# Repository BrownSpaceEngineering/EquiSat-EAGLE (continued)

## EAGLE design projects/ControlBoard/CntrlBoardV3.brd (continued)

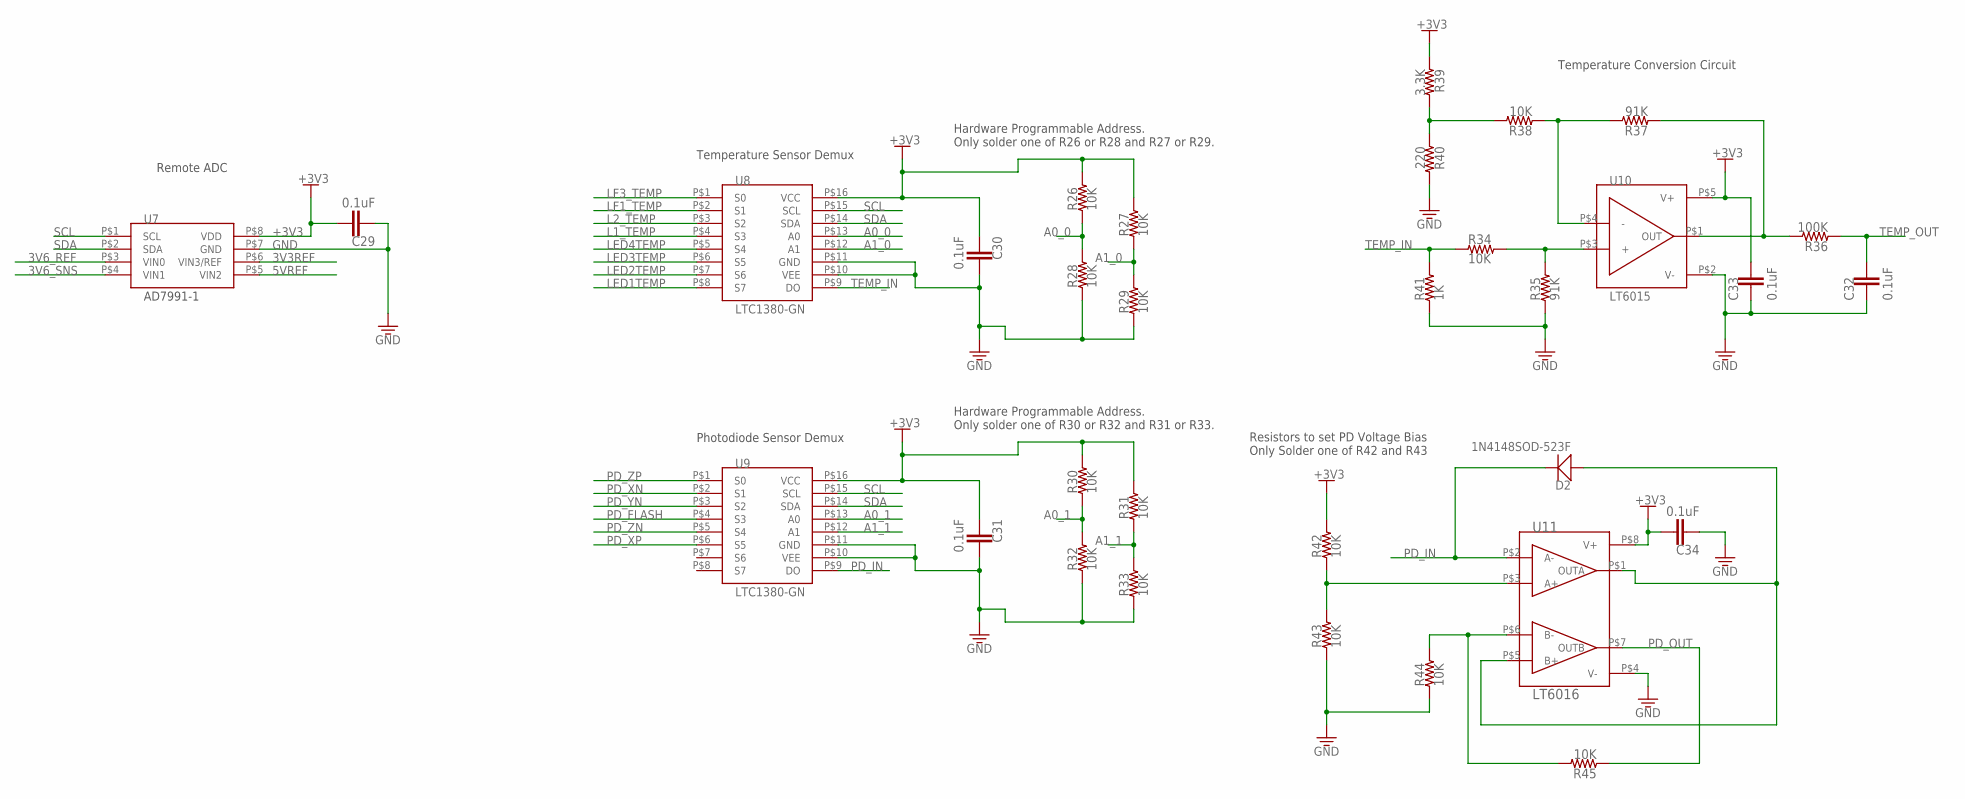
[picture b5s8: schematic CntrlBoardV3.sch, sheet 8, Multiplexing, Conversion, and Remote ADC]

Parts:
C29, C30, C31, C32, C33, C34: 0.1uF; 0805
D2: 1N4148SOD-523F; SOD-523F
R26, R27, R28, R29, R30, R31, R32, R33, R34, R38, R42, R43, R44, R45: 10K; 0805
R35, R37: 91K; 0805
R36: 100K; 0805
R39: 3.3K; 0805
R40: 220; 0805
R41: 1K; 0805
U7: AD7991-1; SOT-23-8
U8, U9: LTC1380-GN; SSOP-16-NARROW
U10: LT6015; TSOT23-5
U11: LT6016; MSOP-8

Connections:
3V3REF: U7.P$6 (VIN3/REF); also elsewhere on the board
3V6_REF: U7.P$3 (VIN0); also elsewhere on the board
3V6_SNS: U7.P$4 (VIN1); also elsewhere on the board
5VREF: U7.P$5 (VIN2); also elsewhere on the board
+3V3: C29.1, C30.2, C31.2, C33.1, C34.1, R26.2, R27.2, R30.2, R31.2, R39.1, R42.2, U7.P$8 (VDD), U8.P$16 (VCC), U9.P$16 (VCC), U10.P$5 (V+), U11.P$8 (V+); also elsewhere on the board
A0_0: R26.1, R28.2, U8.P$13 (A0)
A0_1: R30.1, R32.2, U9.P$13 (A0)
A1_0: R27.1, R29.2, U8.P$12 (A1)
A1_1: R31.1, R33.2, U9.P$12 (A1)
GND: C29.2, C30.1, C31.1, C32.2, C33.2, C34.2, R28.1, R29.1, R32.1, R33.1, R35.1, R40.2, R41.1, R43.1, R44.1, U7.P$7 (GND), U8.P$10 (VEE), U8.P$11 (GND), U9.P$10 (VEE), U9.P$11 (GND), U10.P$2 (V-), U11.P$4 (V-); also elsewhere on the board
L1_TEMP: U8.P$4 (S3); also elsewhere on the board
L2_TEMP: U8.P$3 (S2); also elsewhere on the board
LED1TEMP: U8.P$8 (S7); also elsewhere on the board
LED2TEMP: U8.P$7 (S6); also elsewhere on the board
LED3TEMP: U8.P$6 (S5); also elsewhere on the board
LED4TEMP: U8.P$5 (S4); also elsewhere on the board
LF1_TEMP: U8.P$2 (S1); also elsewhere on the board
LF3_TEMP: U8.P$1 (S0); also elsewhere on the board
unnamed: R34.2, R35.2, U10.P$3 (+)
unnamed: R38.2, R39.2, R40.1
unnamed: R37.2, R38.1, U10.P$4 (-)
unnamed: R36.2, R37.1, U10.P$1 (OUT)
unnamed: D2.A, U11.P$1 (OUTA), U11.P$5 (B+)
unnamed: R42.1, R43.2, U11.P$3 (A+)
unnamed: R44.2, R45.2, U11.P$6 (B-)
PD_FLASH: U9.P$4 (S3); also elsewhere on the board
PD_IN: D2.C, U9.P$9 (DO), U11.P$2 (A-)
PD_OUT: R45.1, U11.P$7 (OUTB); also elsewhere on the board
PD_XN: U9.P$2 (S1); also elsewhere on the board
PD_XP: U9.P$6 (S5); also elsewhere on the board
PD_YN: U9.P$3 (S2); also elsewhere on the board
PD_ZN: U9.P$5 (S4); also elsewhere on the board
PD_ZP: U9.P$1 (S0); also elsewhere on the board
SCL: U7.P$1 (SCL), U8.P$15 (SCL), U9.P$15 (SCL); also elsewhere on the board
SDA: U7.P$2 (SDA), U8.P$14 (SDA), U9.P$14 (SDA); also elsewhere on the board
TEMP_IN: R34.1, R41.2, U8.P$9 (DO)
TEMP_OUT: C32.1, R36.1; also elsewhere on the board

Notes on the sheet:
Hardware Programmable Address. Only solder one of R26 or R28 and R27 or R29.
Temperature Sensor Demux
Hardware Programmable Address. Only solder one of R30 or R32 and R31 or R33.
Photodiode Sensor Demux
Temperature Conversion Circuit
Resistors to set PD Voltage Bias Only Solder one of R42 and R43
Remote ADC

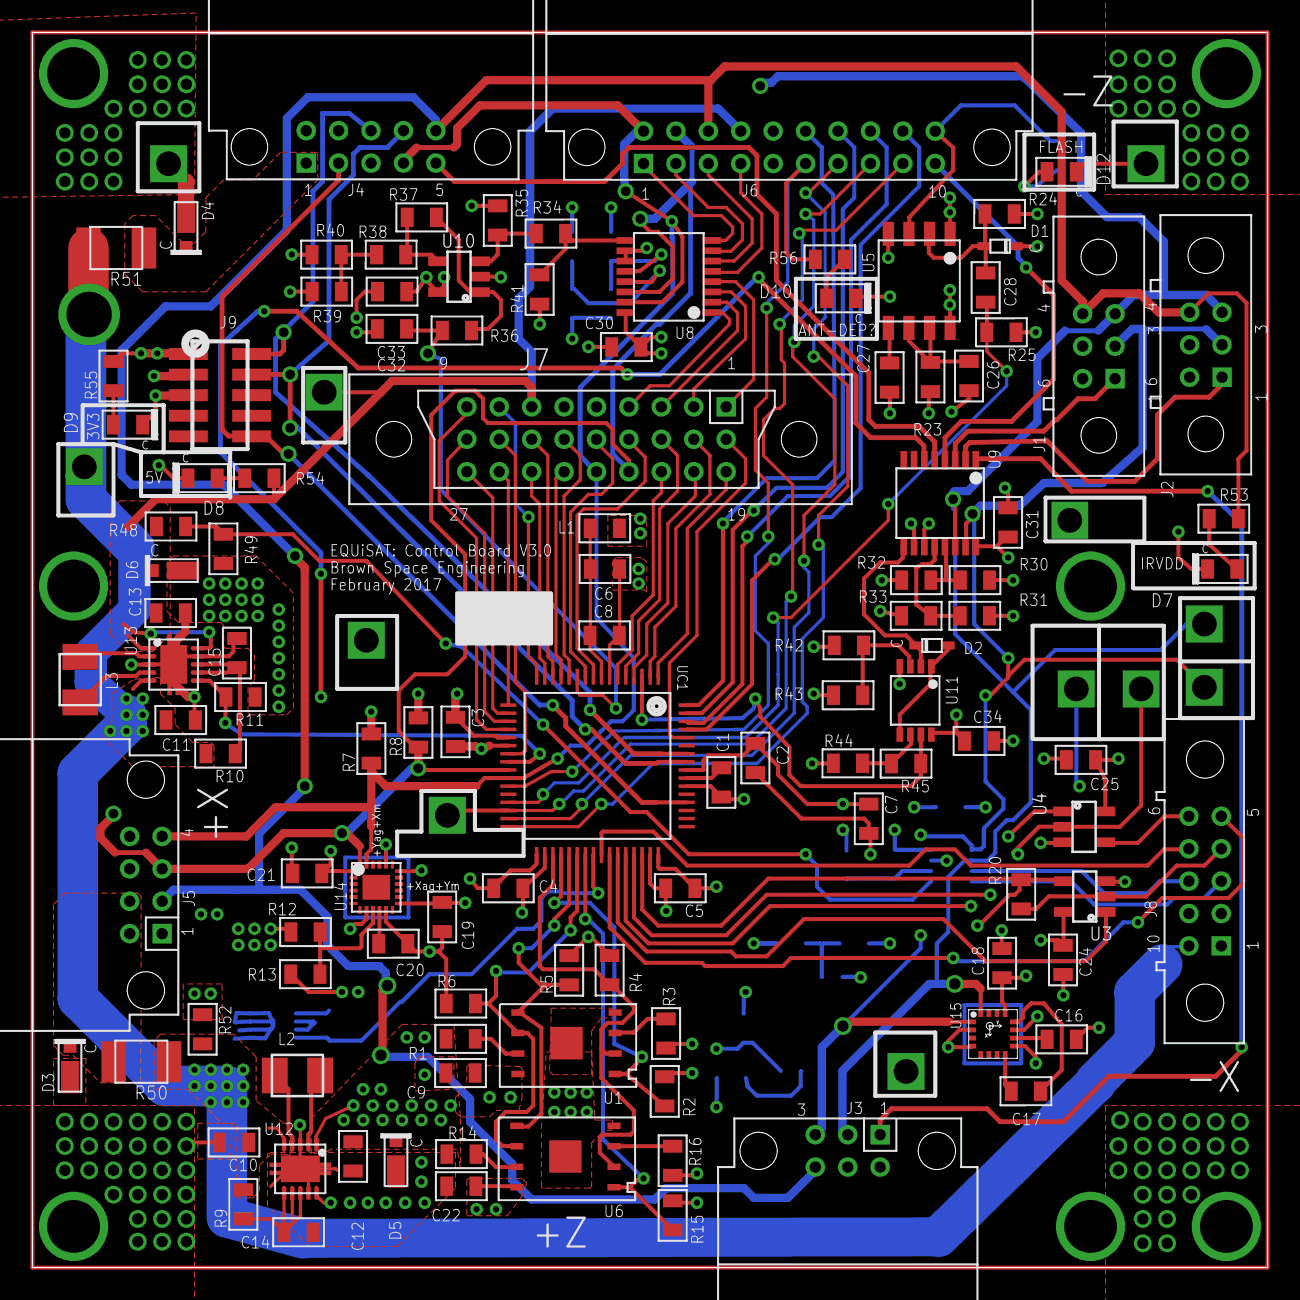
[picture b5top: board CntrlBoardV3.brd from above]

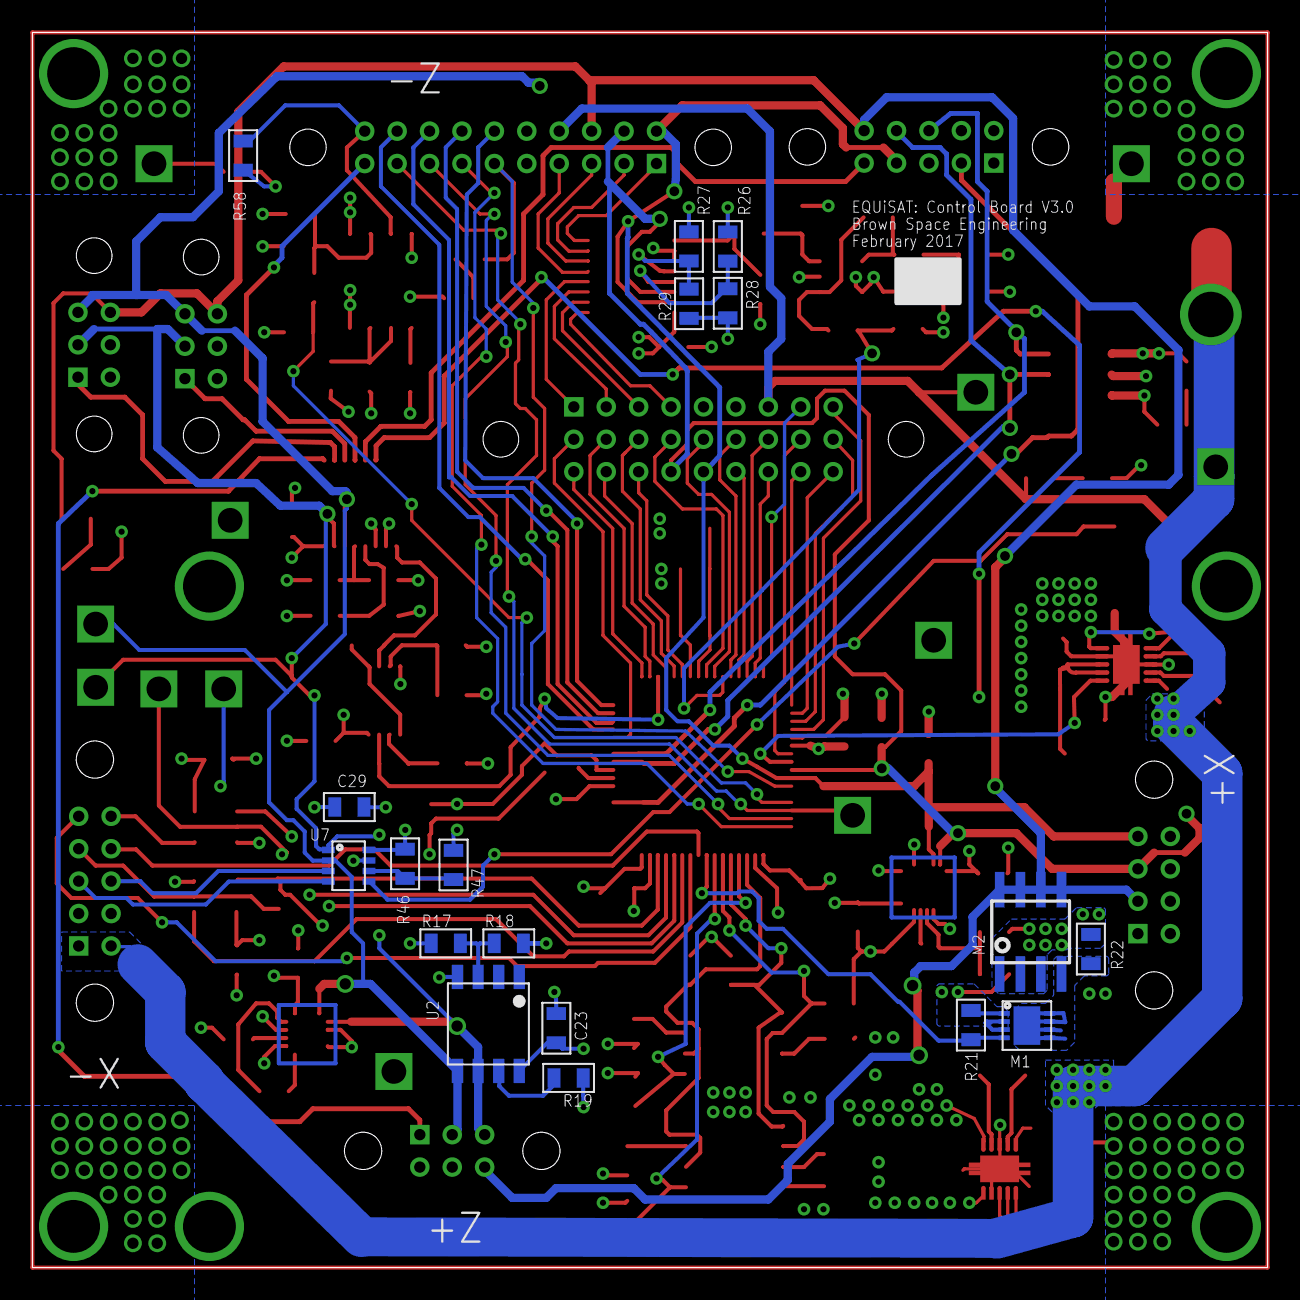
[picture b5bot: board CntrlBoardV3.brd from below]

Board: 4 copper layers, 76.2 x 76.2 mm, 144 parts (18 on the bottom side), 116 nets.
